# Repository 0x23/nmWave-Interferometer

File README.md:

# An Open Source Interferometer for Accurate Distance Measurements

The goal of this project is to provide plans and techniques for building an interferometer that can accurately measure changes in distance over a range of hundreds of millimeters with sub-micrometer precision. The objective is to use low-cost, widely available components and achieve a good balance between ease of manufacturing and performance.

This repository is currently work in progress...

> [!WARNING]
>
> This project involves collimated laser beams with power levels above eye-safe limits able to cause permanent eye damage.
> Please use proper precautions, do your own research, and respect laser safety guidelines.
>
> 

[3D-Printed Grinding Tools](tools_3dprinted/beam_splitter_22mmx13mm)

## Electronics

The KICAD design files for the electronics have been updated to the newest development version. The design is still work in progress but all functions have been successfully tested on a prototype. 

<div style="display: flex; gap: 2%;">

</div>

<!--  -->

## CAD Models

[NEW DESIGN - Version 5] FreeCAD models of the design are now online, take a look! 

## Beam Splitter

The Beam splitter is made from regular float glass with a thickness of about 6 mm. It does not requre any coatings and uses the inherent reflectivity of glass surfaces.
It is ground to size using a diamond wetstone and a series of 3D printed jigs. The models for 3d printing can be found here:

## Laser Diodes

The current recommandation is the: $${\color{lightgreen}Osram \space PLT5 \space 516FA}$$ costing about 12$

For this project the laser source requires a long coherence length, which only certain laser diode models can provide.
Below is a table of laser diodes that I tested or want to test in future:
<br><br>

| Part Number           | Nominal Current | Optimal Drive Current | Power   | Wavelength  | Notes                                             | Plus on case |
|-----------------------|-----------------|-----------------------|---------|-------------|---------------------------------------------------|-----------|
| SLD3232VF             | 55mA            | ?                     | 50mW    | 405nm       | Not good                                          | Yes       |
| QL65E7SA              | 50mA            | 30mA                  | 7mW     | 650nm       | Good                                              | Yes       |
| QL65E7SB or C         | 50mA            | 30mA                  | 7mW     | 650nm       | Good                                              | Yes       |
| PLT520B               | 225mA           | ?                     | 110mW   | 520nm       | Very good (coherence length >4m)                  | Yes       |
| PLT5 516FA            | 100mA           | 36mA                  | 30mW    | 516nm       | (Very) good (CURRENT CHOICE)                      | No        |
| PLT5 520EB_Q          | -               | ?                     | 20mW    | 520nm       | Not tested (datasheet suggests very good)         | No        |
| PLT5 450(G)B          | 80mA            | 21mA                  | 100mW   | 450nm       | Okay                                              | No        |
| PLT5 520DB            | -               | ?                     | 10mW    | 520nm       | Not tested (probably not good)                    | No        |
| PLT5 518FB_P          | -               | ?                     | 30mW    | 518nm       | Not tested (probably not good)                    | No        |

## Photo Diodes

For the project fast photodiodes for the visible spectral range are required. Silicon PIN Photodiodes satisfy these requirements and are readily available.
To get a good signal a small active area of about 1mm² without a lens is prefereable. 

The current choice is the $${\color{lightgreen}SFH229}$$ photodiode in a 3mm LED casing costing about 0.70$.

It is sensitive in the range of 380 nm bis 1100 nm and has a switching time of 10ns. To to reduce the footprint and remove the lense a 3D printed jig and sandpaper can be used.
Mor information on this subject is coming soon..

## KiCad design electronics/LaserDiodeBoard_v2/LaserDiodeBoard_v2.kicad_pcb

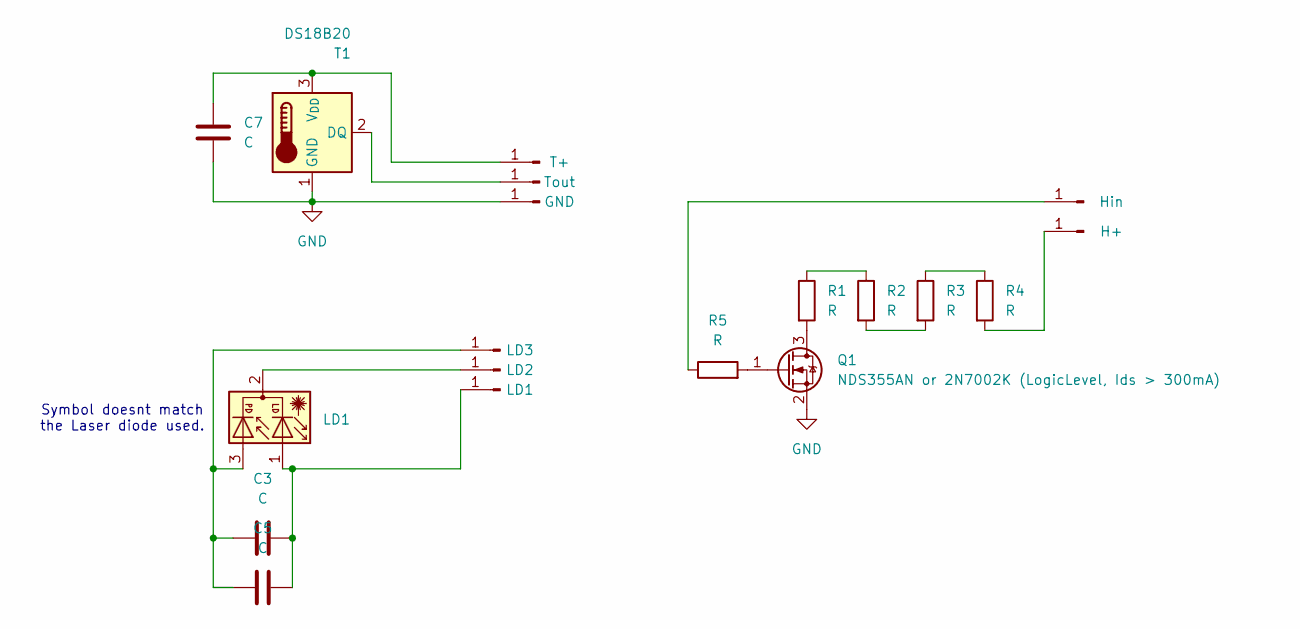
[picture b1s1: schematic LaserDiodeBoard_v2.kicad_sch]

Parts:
C3, C5, C7: C; C_0603_1608Metric_Pad1.08x0.95mm_HandSolder
J1: H+; SolderWirePad_1x01_SMD_1x2mm
J2: Hin; SolderWirePad_1x01_SMD_1x2mm
J3: LD3; SolderWirePad_1x01_SMD_1x2mm
J4: LD2; SolderWirePad_1x01_SMD_1x2mm
J5: LD1; SolderWirePad_1x01_SMD_1x2mm
J6: GND; SolderWirePad_1x01_SMD_1x2mm
J7: Tout; SolderWirePad_1x01_SMD_1x2mm
J8: T+; SolderWirePad_1x01_SMD_1x2mm
LD1: LD; LaserDiode_TO18-D5.6-3
Q1: NDS355AN or 2N7002K (LogicLevel, Ids > 300mA); SOT-23
R1, R2, R3, R4: R; R_0805_2012Metric_Pad1.20x1.40mm_HandSolder
R5: R; R_0603_1608Metric_Pad0.98x0.95mm_HandSolder
T1: DS18B20; TO-92_Inline

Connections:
GND: C7.2, J6.1, Q1.2 (S), T1.1 (GND)
unnamed: J1.1, R4.2
unnamed: J2.1, R5.1
unnamed: C3.1, C5.1, J3.1, LD1.3
unnamed: J4.1, LD1.2
unnamed: C3.2, C5.2, J5.1, LD1.1
unnamed: J7.1, T1.2 (DQ)
unnamed: C7.1, J8.1, T1.3 (V_{DD})
unnamed: Q1.3 (D), R1.2
unnamed: Q1.1 (G), R5.2
unnamed: R1.1, R2.1
unnamed: R2.2, R3.2
unnamed: R3.1, R4.1

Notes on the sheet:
Symbol doesnt match the Laser diode used.

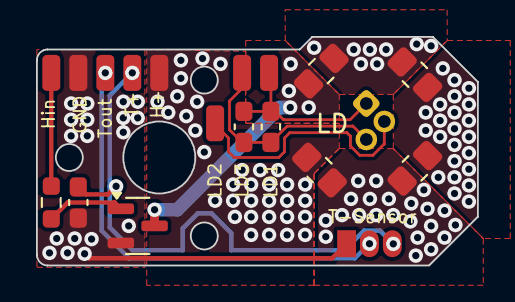
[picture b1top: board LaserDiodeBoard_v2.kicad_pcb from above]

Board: 2 copper layers, 24.5 x 12.7 mm, 19 parts (1 on the bottom side), 13 nets.

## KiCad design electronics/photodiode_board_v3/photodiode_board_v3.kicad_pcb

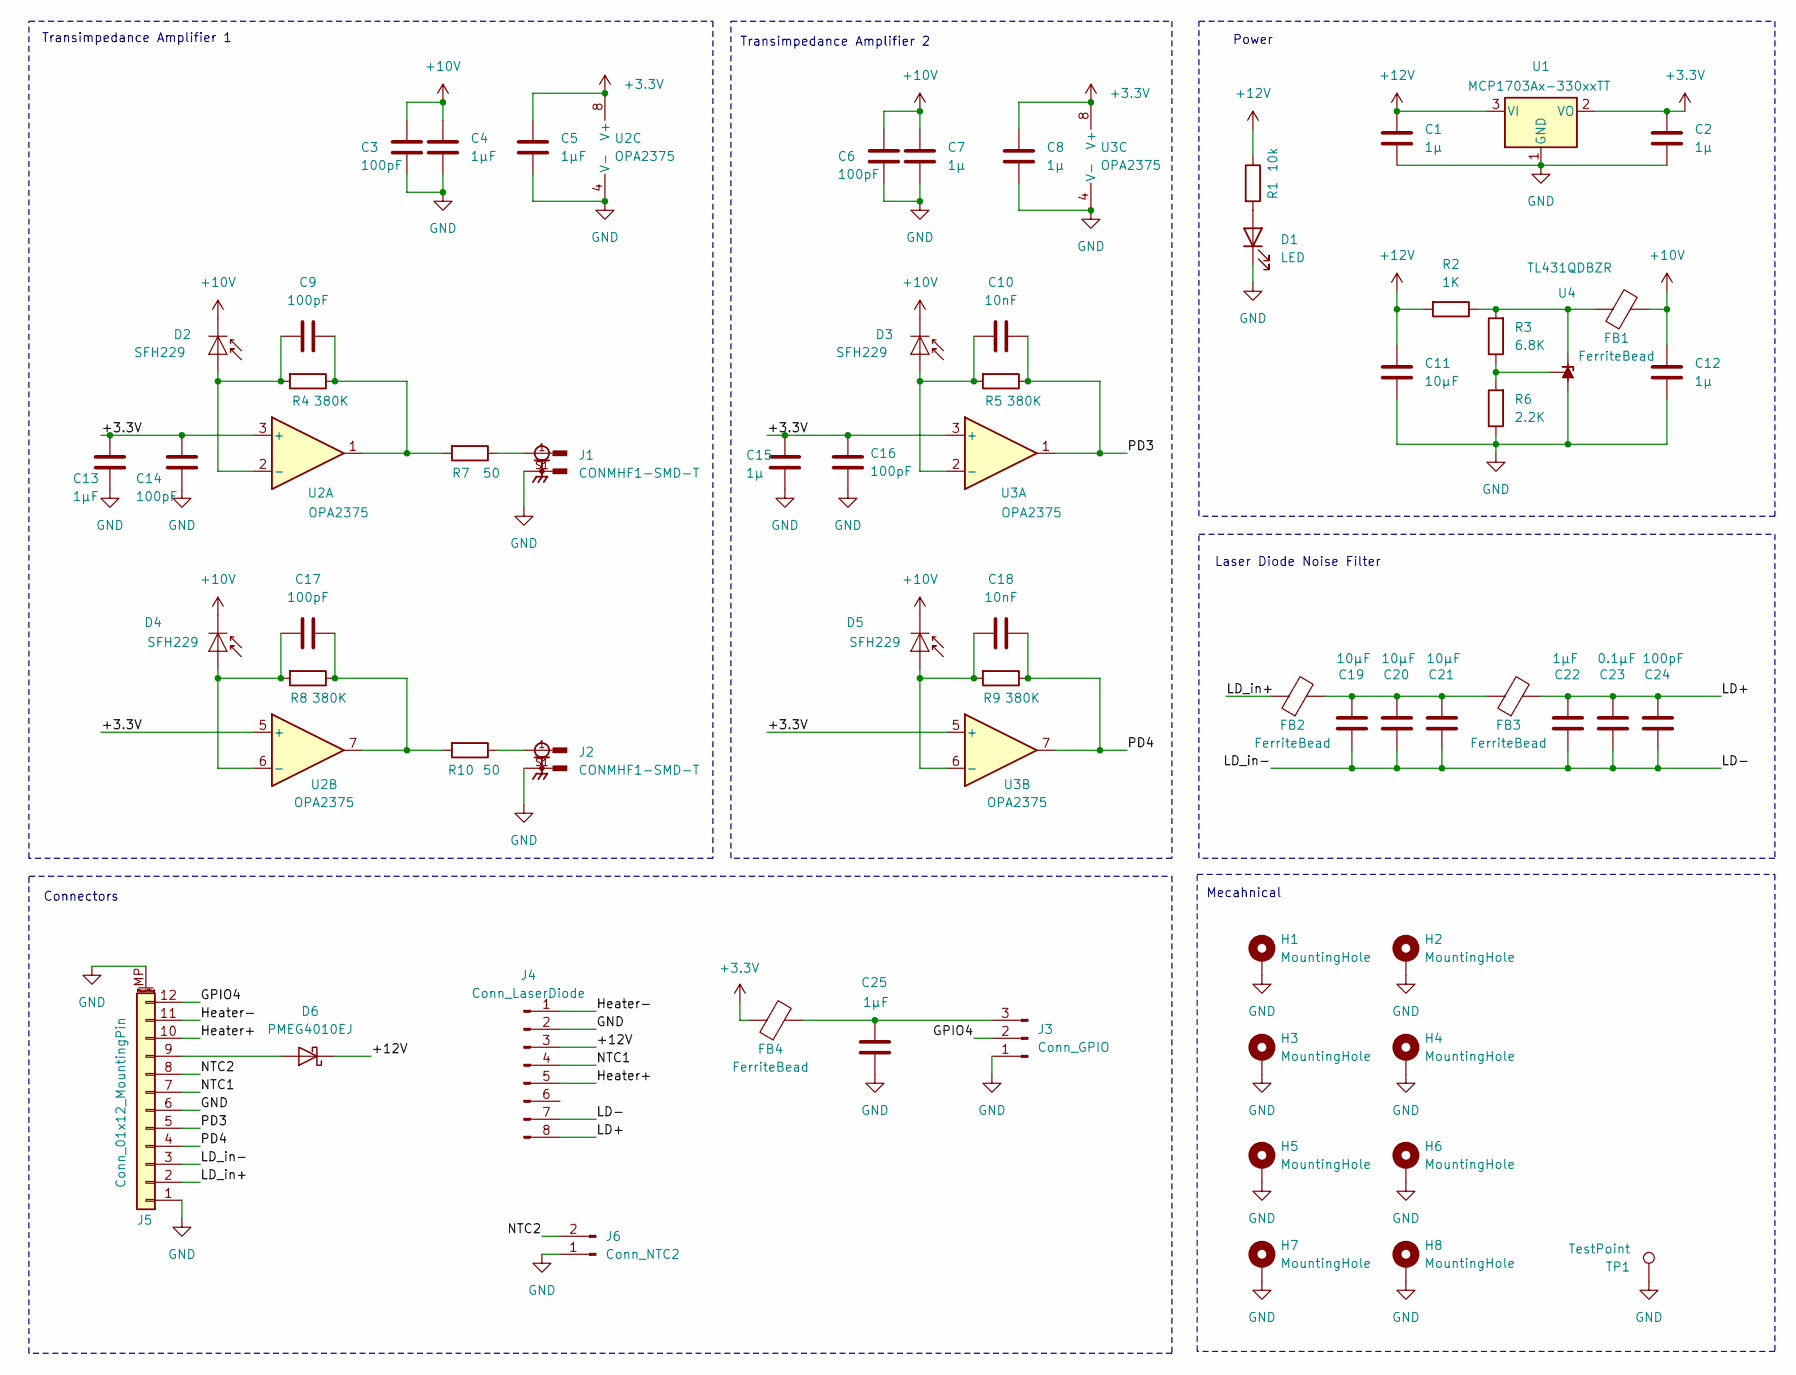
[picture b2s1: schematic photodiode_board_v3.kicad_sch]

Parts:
C1, C2, C7, C8, C12, C15: 1µ; C_0603_1608Metric_Pad1.08x0.95mm_HandSolder
C3, C6, C9, C14, C16, C17, C24: 100pF; C_0603_1608Metric_Pad1.08x0.95mm_HandSolder
C4, C5, C13, C22, C25: 1µF; C_0603_1608Metric_Pad1.08x0.95mm_HandSolder
C10, C18: 10nF; C_0603_1608Metric_Pad1.08x0.95mm_HandSolder
C11, C19, C20, C21: 10µF; C_0805_2012Metric_Pad1.18x1.45mm_HandSolder
C23: 0.1µF; C_0603_1608Metric_Pad1.08x0.95mm_HandSolder
D1: LED; LED_0603_1608Metric_Pad1.05x0.95mm_HandSolder
D2, D3, D4, D5: SFH229; LED_D3.0mm
D6: PMEG4010EJ; D_SOD-323F
FB1, FB2, FB3, FB4: FerriteBead; L_0603_1608Metric
H1, H2, H3, H4, H5, H6, H7, H8: MountingHole; MountingHole_2.7mm_M2.5_ISO7380_Pad
J1, J2: CONMHF1-SMD-T; LINX_CONMHF1-SMD-T
J3: Conn_GPIO; PinHeader_1x03_P2.54mm_Vertical
J4: Conn_LaserDiode; JST_ZH_B8B-ZR_1x08_P1.50mm_Vertical
J5: Conn_01x12_MountingPin; Molex_PicoBlade_53261-1271_1x12-1MP_P1.25mm_Horizontal
J6: Conn_NTC2; PinHeader_1x02_P2.54mm_Vertical
R1: 10k; R_0603_1608Metric_Pad0.98x0.95mm_HandSolder
R2: 1K; R_0603_1608Metric_Pad0.98x0.95mm_HandSolder
R3: 6.8K; R_0603_1608Metric_Pad0.98x0.95mm_HandSolder
R4, R5, R8, R9: 380K; R_0603_1608Metric_Pad0.98x0.95mm_HandSolder
R6: 2.2K; R_0603_1608Metric_Pad0.98x0.95mm_HandSolder
R7, R10: 50; R_0603_1608Metric_Pad0.98x0.95mm_HandSolder
TP1: TestPoint; TestPoint_Bridge_Pitch2.54mm_Drill0.7mm
U1: MCP1703Ax-330xxTT; SOT-23
U2, U3: OPA2375; SOIC-8_3.9x4.9mm_P1.27mm
U4: TL431QDBZR; SOT-23

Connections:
+3.3V: C2.1, C5.1, C8.1, C13.1, C14.1, C15.1, C16.1, FB4.1, U1.2 (VO), U2.3 (+), U2.5 (+), U2.8 (V+), U3.3 (+), U3.5 (+), U3.8 (V+)
+10V: C3.1, C4.2, C6.1, C7.2, C12.1, D2.1 (K), D3.1 (K), D4.1 (K), D5.1 (K), FB1.2
+12V: C1.1, C11.1, D6.1 (K), J4.3, R1.1, R2.2, U1.3 (VI)
/GPIO4: J3.2, J5.12
/Heater+: J4.5, J5.10
/Heater-: J4.1, J5.11
/LD+: C22.2, C23.2, C24.2, FB3.2, J4.8
/LD-: C19.1, C20.1, C21.1, C22.1, C23.1, C24.1, J4.7, J5.3
/LD_in+: FB2.1, J5.2
/NTC1: J4.4, J5.7
/NTC2: J5.8, J6.2
/PD3: C10.2, J5.5, R5.1, U3.1
/PD4: C18.2, J5.4, R9.1, U3.7
GND: C1.2, C2.2, C3.2, C4.1, C5.2, C6.2, C7.1, C8.2, C11.2, C12.2, C13.2, C14.2, C15.2, C16.2, C25.1, D1.1 (K), H1.1, H2.1, H3.1, H4.1, H5.1, H6.1, H7.1, H8.1, J1.S1, J2.S1, J3.1, J4.2, J5.1, J5.6, J5.MP (MountPin), J6.1, R6.1, TP1.1, U1.1 (GND), U2.4 (V-), U3.4 (V-), U4.3 (A)
unnamed: C9.2, R4.1, R7.2, U2.1
unnamed: C17.2, R8.1, R10.2, U2.7
unnamed: C19.2, C20.2, C21.2, FB2.2, FB3.1
unnamed: D1.2 (A), R1.2
unnamed: C9.1, D2.2 (A), R4.2, U2.2 (-)
unnamed: C10.1, D3.2 (A), R5.2, U3.2 (-)
unnamed: C17.1, D4.2 (A), R8.2, U2.6 (-)
unnamed: C18.1, D5.2 (A), R9.2, U3.6 (-)
unnamed: D6.2 (A), J5.9
unnamed: J1.1, R7.1
unnamed: J2.1, R10.1
unnamed: C25.2, FB4.2, J3.3
unnamed: FB1.1, R2.1, R3.2, U4.1 (K)
unnamed: R3.1, R6.2, U4.2 (REF)

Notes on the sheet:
Transimpedance Amplifier 2
Transimpedance Amplifier 1
Connectors
Power
Laser Diode Noise Filter
Mecahnical

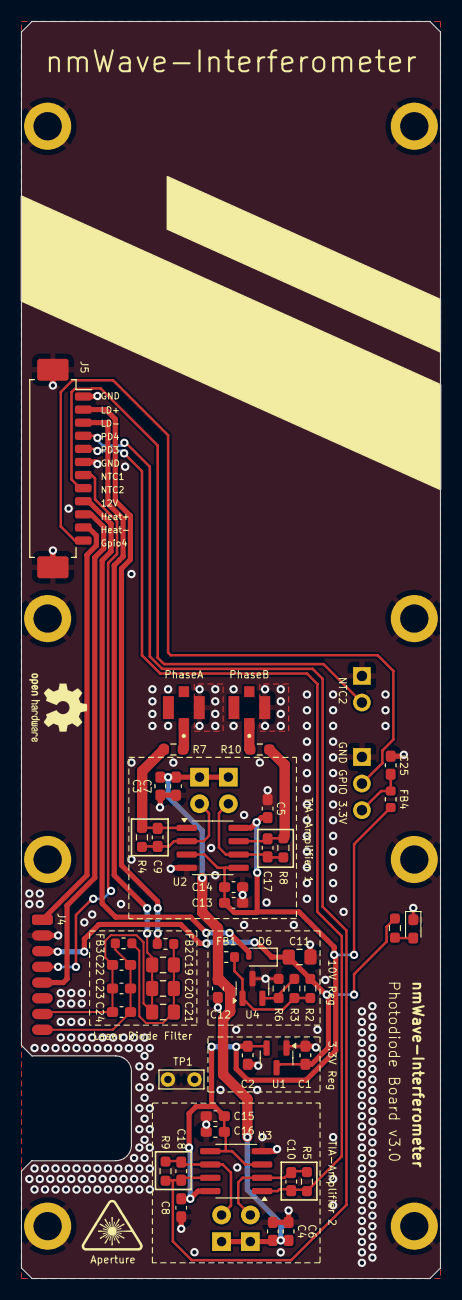
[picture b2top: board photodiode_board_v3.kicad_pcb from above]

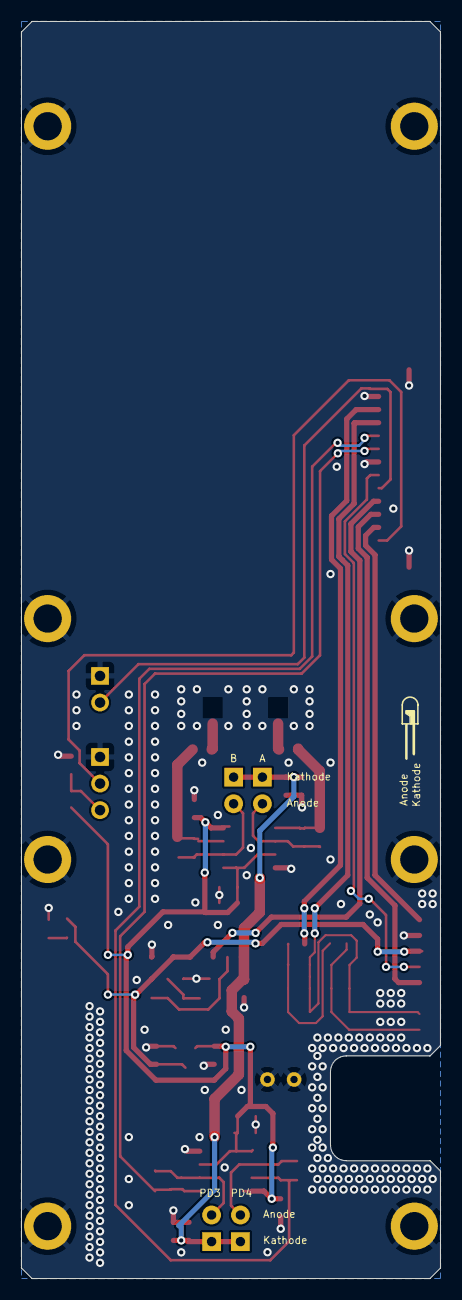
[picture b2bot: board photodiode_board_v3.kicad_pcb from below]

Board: 2 copper layers, 40.0 x 120.0 mm, 64 parts (4 on the bottom side), 28 nets.

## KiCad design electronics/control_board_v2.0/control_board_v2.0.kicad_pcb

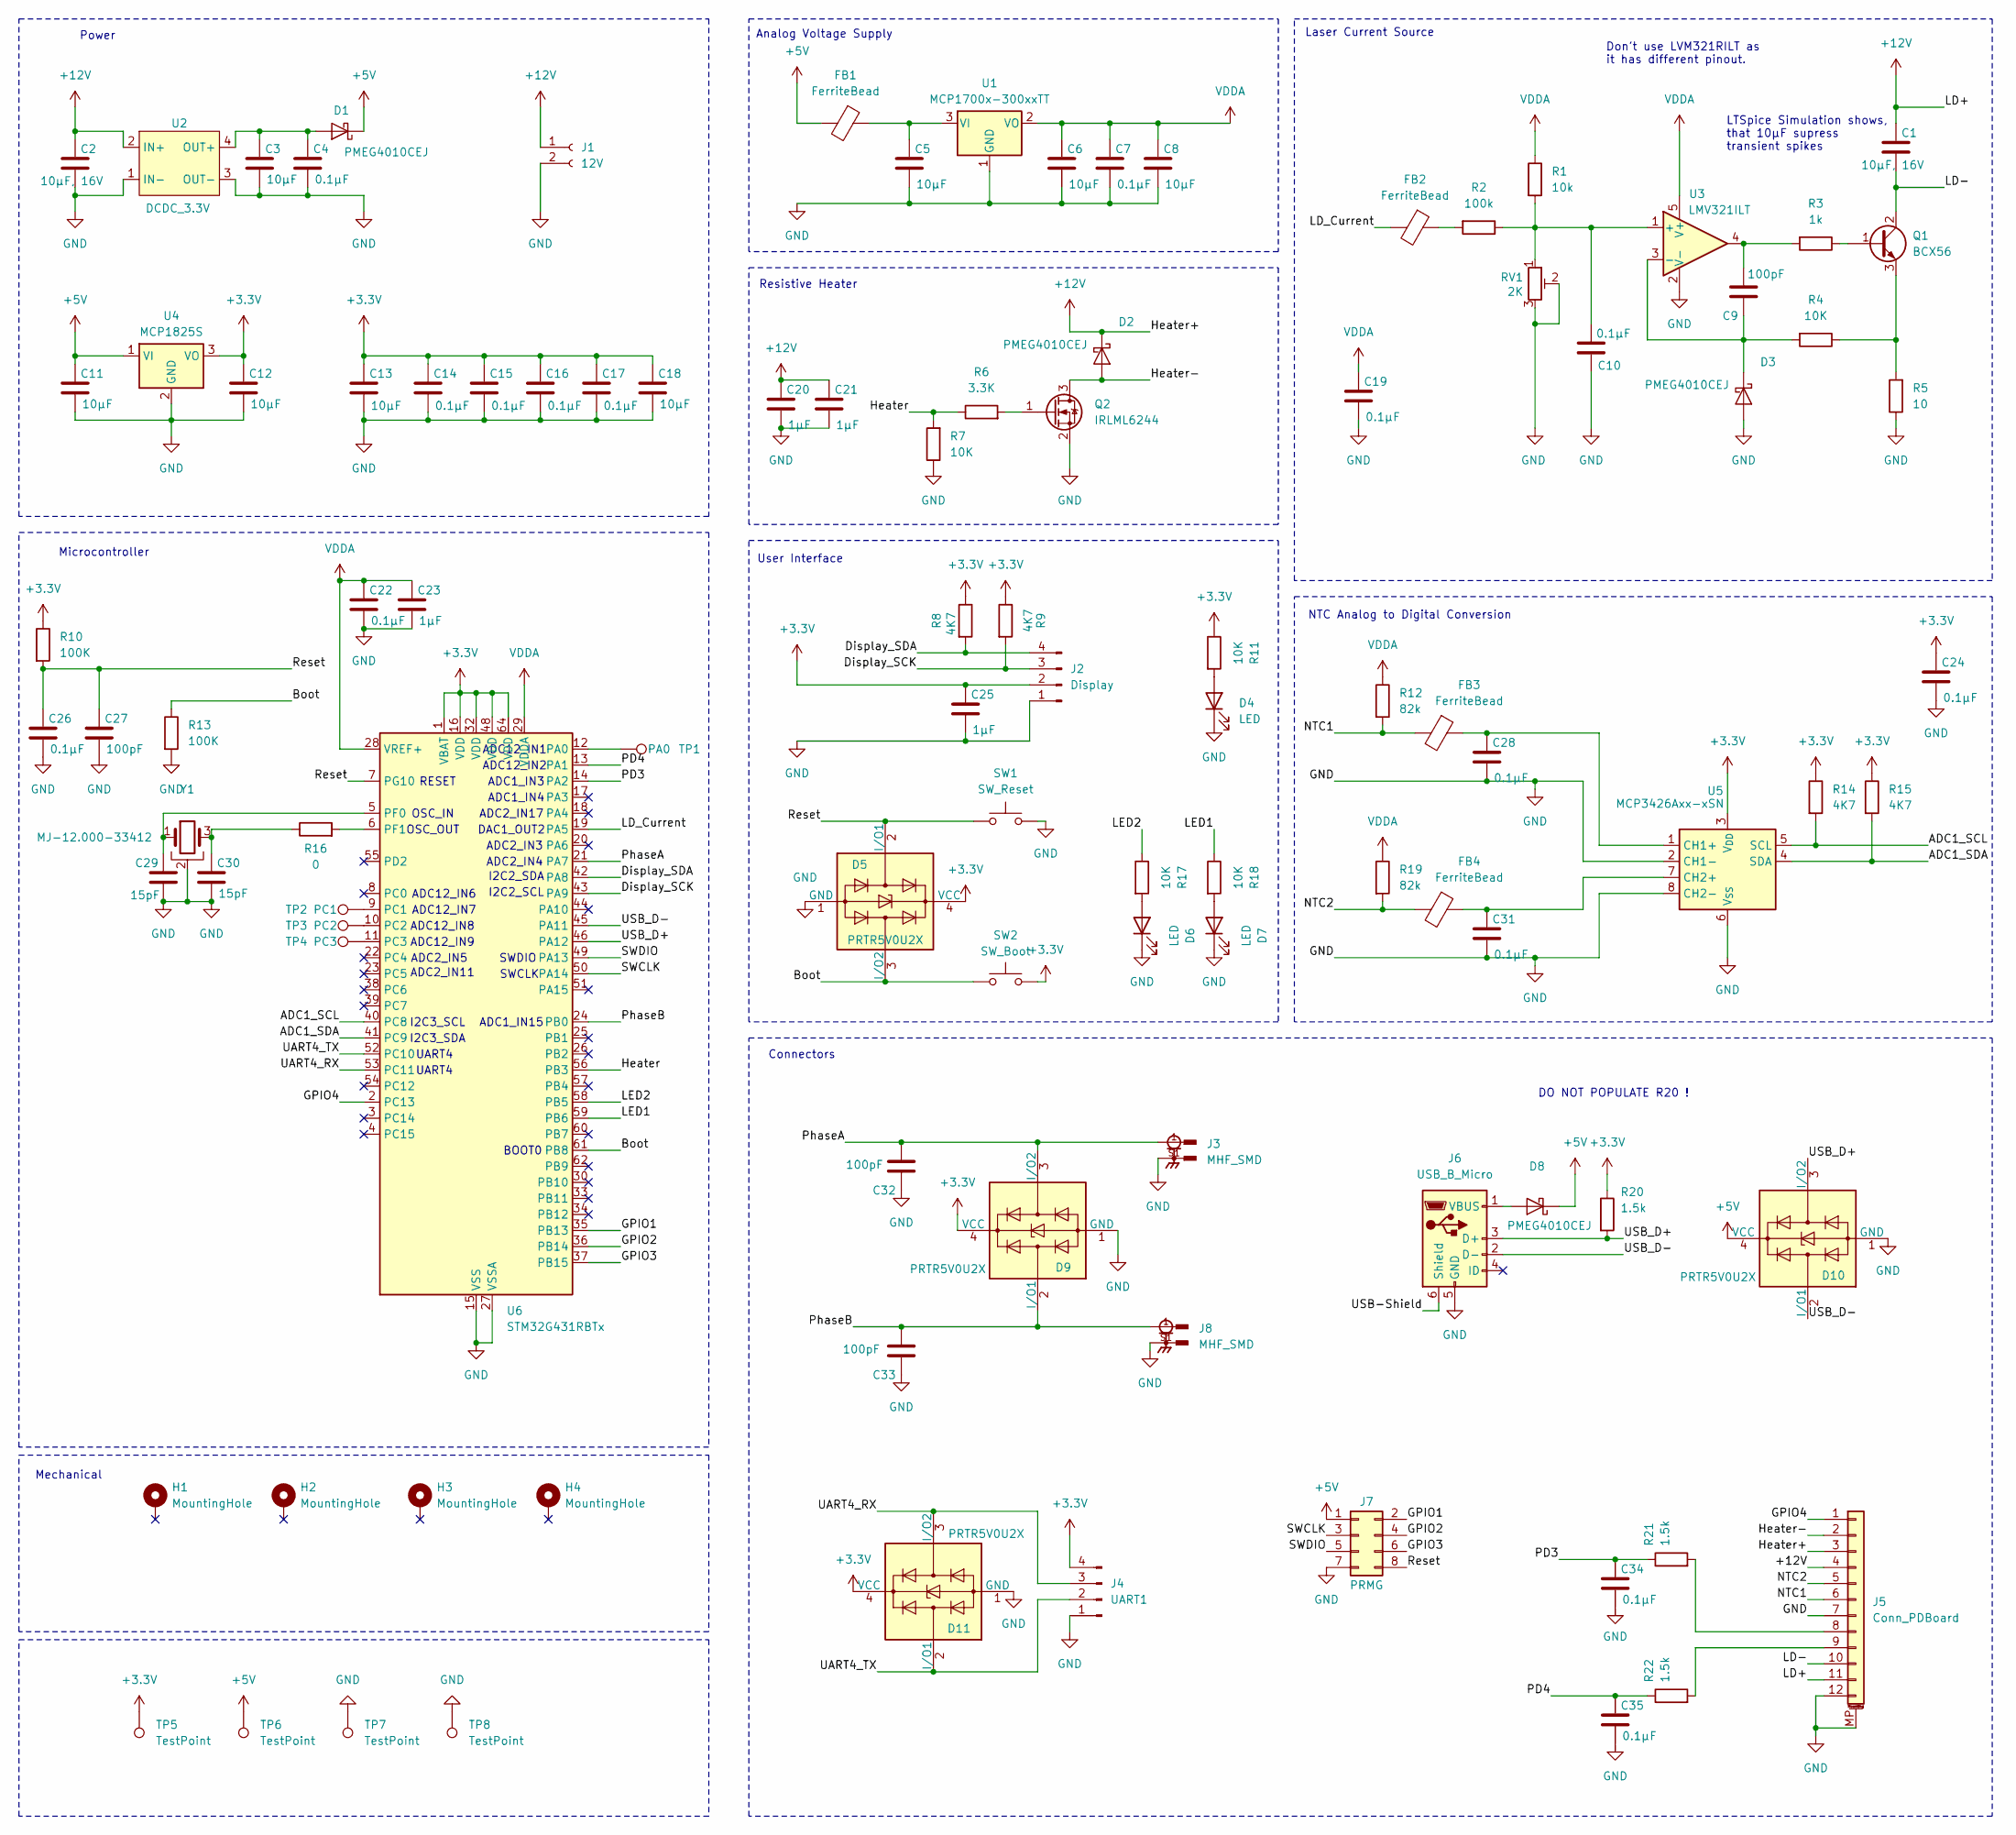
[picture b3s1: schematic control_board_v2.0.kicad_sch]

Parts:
C1, C2: 10µF, 16V; C_0805_2012Metric
C3, C5, C6, C8, C11, C12, C13, C18: 10µF; C_0603_1608Metric
C4, C7, C10, C14, C15, C16, C17, C19, C22, C24, C26, C28, C31, C34, C35: 0.1µF; C_0603_1608Metric
C9, C27, C32, C33: 100pF; C_0603_1608Metric
C20, C21, C23, C25: 1µF; C_0603_1608Metric
C29, C30: 15pF; C_0603_1608Metric
D1, D2, D3, D8: PMEG4010CEJ; D_SOD-323F
D4, D6, D7: LED; LED_0603_1608Metric_Pad1.05x0.95mm_HandSolder
D5, D9, D10, D11: PRTR5V0U2X; SOT-143
FB1, FB2, FB3, FB4: FerriteBead; L_0603_1608Metric
H1, H2, H3, H4: MountingHole; MountingHole_2.7mm_M2.5_ISO14580_Pad
J1: 12V; AMASS_XT30U-F_1x02_P5.0mm_Vertical
J2: Display; PinHeader_1x04_P2.54mm_Vertical
J3, J8: MHF_SMD; LINX_CONMHF1-SMD-T
J4: UART1; JST_PH_B4B-PH-K_1x04_P2.00mm_Vertical
J5: Conn_PDBoard; Molex_PicoBlade_53261-1271_1x12-1MP_P1.25mm_Horizontal
J6: USB_B_Micro; USB_Micro-B_Amphenol_10118194_Horizontal
J7: PRMG; PinHeader_2x04_P2.54mm_Vertical
Q1: BCX56; SOT-89-3
Q2: IRLML6244; SOT-23
R1: 10k; R_0603_1608Metric
R2: 100k; R_0603_1608Metric
R3: 1k; R_0603_1608Metric
R4, R7, R11, R17, R18: 10K; R_0603_1608Metric
R5: 10; R_MiniMELF_MMA-0204
R6: 3.3K; R_0603_1608Metric
R8, R9, R14, R15: 4K7; R_0603_1608Metric
R10, R13: 100K; R_0603_1608Metric
R12, R19: 82k; R_0603_1608Metric
R16: 0; R_0603_1608Metric
R20, R21, R22: 1.5k; R_0603_1608Metric
RV1: 2K; Potentiometer_Bourns_3266X_Horizontal
SW1: SW_Reset; SW_SPST_SKQG_WithoutStem
SW2: SW_Boot; SW_SPST_SKQG_WithoutStem
TP1: PA0; TestPoint_THTPad_D1.0mm_Drill0.5mm
TP2: PC1; TestPoint_THTPad_D1.0mm_Drill0.5mm
TP3: PC2; TestPoint_THTPad_D1.0mm_Drill0.5mm
TP4: PC3; TestPoint_THTPad_D1.0mm_Drill0.5mm
TP5, TP6, TP7: TestPoint; TestPoint_THTPad_D1.0mm_Drill0.5mm
TP8: TestPoint; TestPoint_Bridge_Pitch2.54mm_Drill0.7mm
U1: MCP1700x-300xxTT; SOT-23
U2: DCDC_3.3V; DCDC_17mmx12mm
U3: LMV321ILT; SOT-23-5
U4: MCP1825S; SOT-223-3_TabPin2
U5: MCP3426Axx-xSN; SOIC-8_3.9x4.9mm_P1.27mm
U6: STM32G431RBTx; LQFP-64_10x10mm_P0.5mm
Y1: MJ-12.000-33412; Crystal_SMD_5032-4Pin_5.0x3.2mm

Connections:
+3.3V: C12.1, C13.1, C14.1, C15.1, C16.1, C17.1, C18.1, C24.1, C25.1, D5.4 (VCC), D9.4 (VCC), D11.4 (VCC), J2.2, J4.4, R8.1, R9.1, R10.1, R11.1, R14.1, R15.1, R20.1, SW2.2, TP5.1, U4.3 (VO), U5.3 (V_{DD}), U6.1 (VBAT), U6.16 (VDD), U6.32 (VDD), U6.48 (VDD), U6.64 (VDD)
+5V: C11.1, D1.1 (K), D8.1 (K), D10.4 (VCC), FB1.2, J7.1, TP6.1, U4.1 (VI)
+12V: C1.1, C2.1, C20.1, C21.1, D2.1 (K), J1.1, J5.3, J5.4, J5.11, U2.2 (IN+)
/ADC1_SCL: R14.2, U5.5 (SCL), U6.40 (PC8)
/ADC1_SDA: R15.2, U5.4 (SDA), U6.41 (PC9)
/Boot: D5.3 (I/O2), R13.1, SW2.1, U6.61 (PB8)
/Display_SCK: J2.3, R9.2, U6.43 (PA9)
/Display_SDA: J2.4, R8.2, U6.42 (PA8)
/GPIO1: J7.2, U6.35 (PB13)
/GPIO2: J7.4, U6.36 (PB14)
/GPIO3: J7.6, U6.37 (PB15)
/GPIO4: J5.1, U6.2 (PC13)
/Heater: R6.1, R7.2, U6.56 (PB3)
/Heater-: D2.2 (A), J5.2, Q2.3 (D)
/LD-: C1.2, J5.10, Q1.2 (C)
/LD_Current: FB2.2, U6.19 (PA5)
/LED1: R18.1, U6.59 (PB6)
/LED2: R17.1, U6.58 (PB5)
/NTC1: FB3.2, J5.6, R12.2
/NTC2: FB4.2, J5.5, R19.2
/PD3: C34.1, R21.1, U6.14 (PA2)
/PD4: C35.1, R22.1, U6.13 (PA1)
/PhaseA: C32.2, D9.3 (I/O2), J3.1, U6.21 (PA7)
/PhaseB: C33.2, D9.2 (I/O1), J8.1, U6.24 (PB0)
/Reset: C26.1, C27.1, D5.2 (I/O1), J7.8, R10.2, SW1.1, U6.7 (PG10)
/SWCLK: J7.3, U6.50 (PA14)
/SWDIO: J7.5, U6.49 (PA13)
/UART4_RX: D11.3 (I/O2), J4.3, U6.53 (PC11)
/UART4_TX: D11.2 (I/O1), J4.2, U6.52 (PC10)
/USB-Shield: J6.6 (Shield)
/USB_D+: D10.3 (I/O2), J6.3 (D+), R20.2, U6.46 (PA12)
/USB_D-: D10.2 (I/O1), J6.2 (D-), U6.45 (PA11)
GND: C2.2, C3.2, C4.2, C5.2, C6.2, C7.2, C8.2, C10.1, C11.2, C12.2, C13.2, C14.2, C15.2, C16.2, C17.2, C18.2, C19.2, C20.2, C21.2, C22.2, C23.2, C24.2, C25.2, C26.2, C27.2, C28.2, C29.2, C30.2, C31.2, C32.1, C33.1, C34.2, C35.2, D3.2 (A), D4.1 (K), D5.1 (GND), D6.1 (K), D7.1 (K), D9.1 (GND), D10.1 (GND), D11.1 (GND), J1.2, J2.1, J3.S1, J4.1, J5.7, J5.12, J5.MP (MountPin), J6.5 (GND), J7.7, J8.S1, Q2.2 (S), R5.1, R7.1, R13.2, RV1.2, RV1.3, SW1.2, TP7.1, TP8.1, U1.1 (GND), U2.1 (IN-), U2.3 (OUT-), U3.2 (V-), U4.2 (GND), U5.2 (CH1-), U5.6 (V_{SS}), U5.8 (CH2-), U6.15 (VSS), U6.27 (VSSA), U6.31 (VSS), U6.47 (VSS), U6.63 (VSS), Y1.2
unnamed: C9.2, R3.2, U3.4
unnamed: C30.1, R16.1, Y1.3
unnamed: C3.1, C4.1, D1.2 (A), U2.4 (OUT+)
unnamed: C9.1, D3.1 (K), R4.2, U3.3 (-)
unnamed: D4.2 (A), R11.2
unnamed: D6.2 (A), R17.2
unnamed: D7.2 (A), R18.2
unnamed: D8.2 (A), J6.1 (VBUS)
unnamed: FB2.1, R2.2
unnamed: J5.8, R21.2
unnamed: J5.9, R22.2
unnamed: Q1.1 (B), R3.1
unnamed: Q1.3 (E), R4.1, R5.2
unnamed: Q2.1 (G), R6.2
unnamed: C5.1, FB1.1, U1.3 (VI)
unnamed: C10.2, R1.2, R2.1, RV1.1, U3.1 (+)
unnamed: C28.1, FB3.1, U5.1 (CH1+)
unnamed: C31.1, FB4.1, U5.7 (CH2+)
unnamed: TP1.1, U6.12 (PA0)
unnamed: TP2.1, U6.9 (PC1)
unnamed: TP3.1, U6.10 (PC2)
unnamed: TP4.1, U6.11 (PC3)
unnamed: C29.1, U6.5 (PF0), Y1.1
unnamed: R16.2, U6.6 (PF1)
VDDA: C6.1, C7.1, C8.1, C19.1, C22.1, C23.1, R1.1, R12.1, R19.1, U1.2 (VO), U3.5 (V+), U6.28 (VREF+), U6.29 (VDDA)

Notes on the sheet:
SWCLK
ADC1_IN4
Don't use LVM321RILT as it has different pinout.
ADC12_IN8
I2C2_SDA
ADC12_IN2
ADC12_IN7
ADC2_IN17
I2C3_SCL
Laser Current Source
ADC1_IN15
SWDIO
OSC_IN
ADC2_IN11
ADC2_IN3
Resistive Heater
ADC2_IN4
Microcontroller
OSC_OUT
ADC2_IN5
ADC12_IN1
UART4
BOOT0
ADC1_IN3
Power
Mechanical
I2C2_SCL
NTC Analog to Digital Conversion
DO NOT POPULATE R20 !
Connectors
LTSpice Simulation shows, that 10µF supress transient spikes
RESET
ADC12_IN9
Analog Voltage Supply
DAC1_OUT2
User Interface
I2C3_SDA
ADC12_IN6

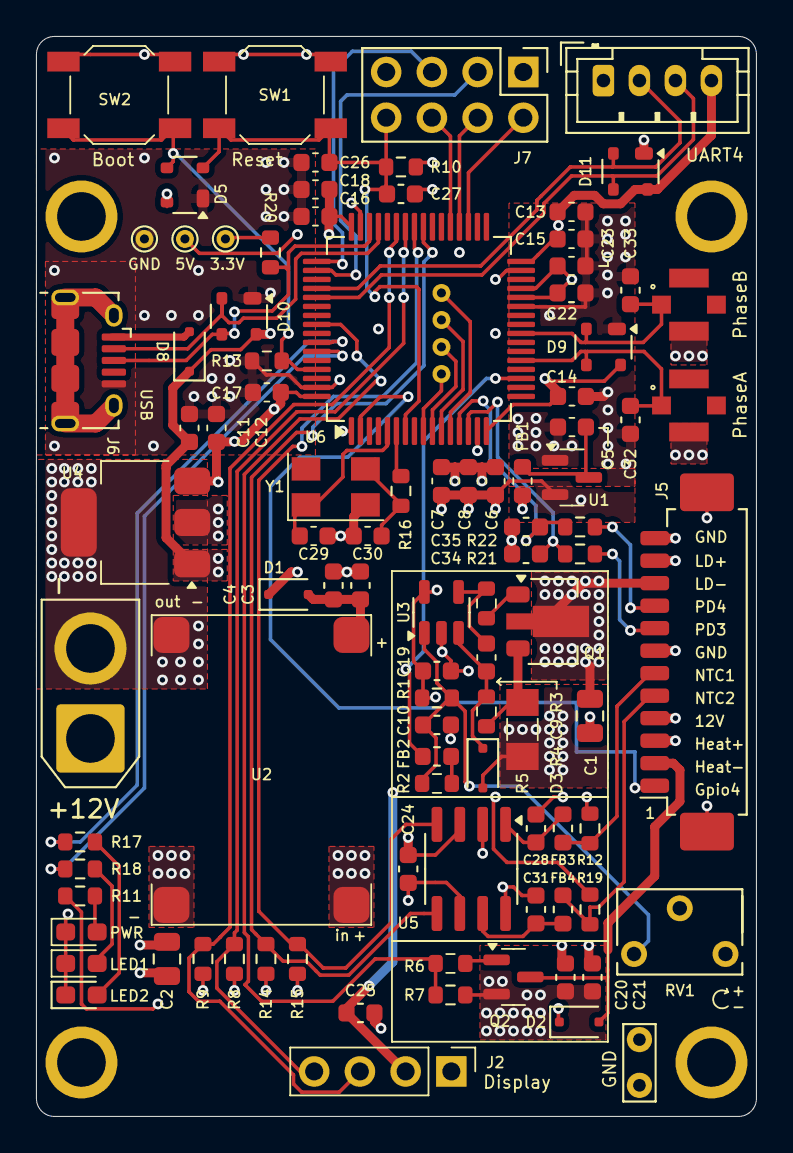
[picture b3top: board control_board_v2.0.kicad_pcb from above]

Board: 4 copper layers, 40.0 x 60.0 mm, 104 parts (0 on the bottom side), 57 nets.

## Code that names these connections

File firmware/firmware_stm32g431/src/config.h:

#define PIN_LED1 PB6
#define PIN_LED2 PB5

#define PIN_PHASE_A PA7   // PhaseA - photo diode input 
#define PIN_PHASE_B PB0   // PhaseB - photo diode input
#define PIN_PHOTODIODE_3 PA2
#define PIN_PHOTODIODE_4 PA1
#define PIN_HEATER PB3

#define ADC1_SCL PC8
#define ADC1_SDA PC9
#define LD_CURRENT PA5    // laser diode current modulation analog out

#define UART4_TX PC10
#define UART4_RX PC11

#define DISPLAY_SDA PA8
#define DISPLAY_SCL PA9

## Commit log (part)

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2024-11-11 added images
2024-11-14 added 3d printed tools
2024-11-15 added tool mesh
2024-11-22 image replaced
2025-03-19 FreeCAD files of new design added
2025-04-11 new mechanical design (version 5)
2025-04-11 update image
2025-04-18 added first version of the base board for community review
2025-04-18 added missing cad file
2025-04-18 added mcu closeup
2025-09-03 board review files
2026-02-21 Added current version of electronics. Its still work in progress.
2026-02-21 updated images
